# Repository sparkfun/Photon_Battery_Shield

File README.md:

SparkFun Photon Battery Shield
========================================

[*SparkFun Photon Battery Shield (DEV-13626)*](https://www.sparkfun.com/products/13626)

The [SparkFun Photon Battery Shield](https://www.sparkfun.com/products/13231) provides you with an easy way to power your Photon module with a Lithium polymer battery. Not only can the Battery Shield power you Photon but you will also be able to charge a LiPo bettery through it as well. The board comes with a JST connector for your single cell LiPo battery and utilizes the Photons on-board micro-USB connector for the charge input.

This battery shield uses a MCP73831 for LiPo charging and a MAX1704X for fuel gauging.

Repository Contents
-------------------

* **/Hardware** - Eagle design files (.brd, .sch)
* **/Production** - Production panel files (.brd)
* **/Libraries** - Firmware library and example code for the Particle Photon.

Documentation
--------------
* **[Hookup Guide](https://learn.sparkfun.com/tutorials/photon-battery-shield-hookup-guide)** - Hardware overview and example code.

Product Versions
----------------
* [DEV-13626](https://www.sparkfun.com/products/13626)- V1.0 release of the Photon Battery Shield.

License Information
-------------------
This product is _**open source**_! 

The **hardware** is released under [Creative Commons ShareAlike 4.0 International](https://creativecommons.org/licenses/by-sa/4.0/).

The **code**  license can be found in the source directory.

Please use, reuse, and modify these files as you see fit. Please maintain attribution to SparkFun Electronics and release anything derivative under the same license.

Distributed as-is; no warranty is given.

- Your friends at SparkFun.

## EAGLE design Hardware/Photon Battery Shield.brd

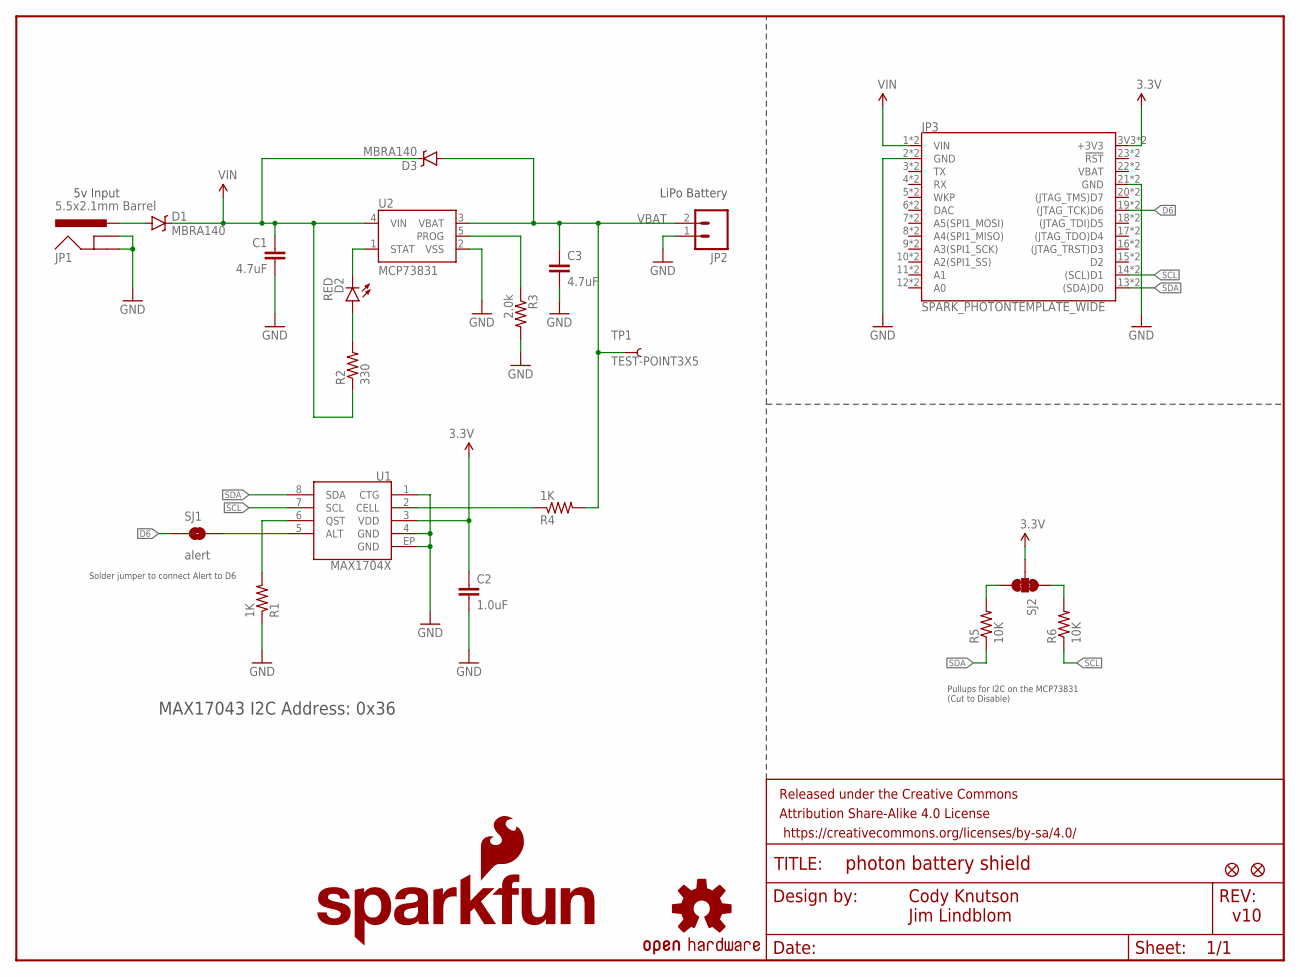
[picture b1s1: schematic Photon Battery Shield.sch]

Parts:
C1, C3: 4.7uF; 0603-CAP
C2: 1.0uF; 0603-CAP
D1, D3: MBRA140; SMA-DIODE
D2: RED; LED-0603
FID1, FID2: FIDUCIAL1X2; FIDUCIAL-1X2
FRAME1: FRAME-LETTER; CREATIVE_COMMONS
JP1: 5.5x2.1mm Barrel; POWER_JACK_SMD
JP2: M02-JST-2MM-SMT; JST-2-SMD
JP3: SPARK_PHOTONTEMPLATE_WIDE; SPARK_PHOTON_TEMPLATE_WIDE
LOGO2: OSHW-LOGOS; OSHW-LOGO-S
LOGO3: SFE_LOGO_NAME_FLAME.1_INCH; SFE_LOGO_NAME_FLAME_.1
R1, R4: 1K; 0603-RES
R2: 330; 0603-RES
R3: 2.0k; 0603-RES
R5, R6: 10K; 0603-RES
SJ1: alert; PAD-JUMPER-2-NO_YES_SILK
SJ2: JUMPER-PAD-3-NC_BY_TRACE; PAD-JUMPER-3-3OF3_NC_BY_TRACE_YES_SILK_FULL_BOX
TP1: TEST-POINT3X5; PAD.03X.05
U1: MAX1704X; TDFN-8
U2: MCP73831; SOT23-5

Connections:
3.3V: C2.1, JP3.3V3 (+3V3), JP3.24 (+3V3), SJ2.2, U1.3 (VDD)
D6: JP3.19 ((JTAG_TCK)D6), JP3.D6 ((JTAG_TCK)D6), SJ1.1
GND: C1.2, C2.2, C3.2, JP1.GND (GNDBREAK), JP1.P$4 (GND), JP2.1 (2), JP3.2 (GND), JP3.21 (GND), JP3.GND@0 (GND), JP3.GND@2 (GND), R1.1, R3.2, U1.1 (CTG), U1.4 (GND), U1.EP (GND), U2.2 (VSS)
unnamed: D2.A, R2.2
unnamed: D2.C, U2.1 (STAT)
unnamed: R3.1, U2.5 (PROG)
unnamed: SJ1.2, U1.5 (ALT)
unnamed: R4.1, U1.2 (CELL)
unnamed: R1.2, U1.6 (QST)
unnamed: R5.2, SJ2.3
unnamed: D1.A, JP1.VIN0 (PWR)
unnamed: R6.2, SJ2.1
SCL: JP3.14 ((SCL)D1), JP3.D1 ((SCL)D1), R6.1, U1.7 (SCL)
SDA: JP3.13 ((SDA)D0), JP3.D0 ((SDA)D0), R5.1, U1.8 (SDA)
VBAT: C3.1, D3.A, JP2.2 (1), R4.2, TP1.P$1, U2.3 (VBAT)
VIN: C1.1, D1.C, D3.C, JP3.1 (VIN), JP3.VIN, R2.1, U2.4 (VIN)

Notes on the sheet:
LiPo Battery
Cody Knutson Jim Lindblom
v10
MAX17043 I2C Address: 0x36
5v Input
Solder jumper to connect Alert to D6
Pullups for I2C on the MCP73831 (Cut to Disable)

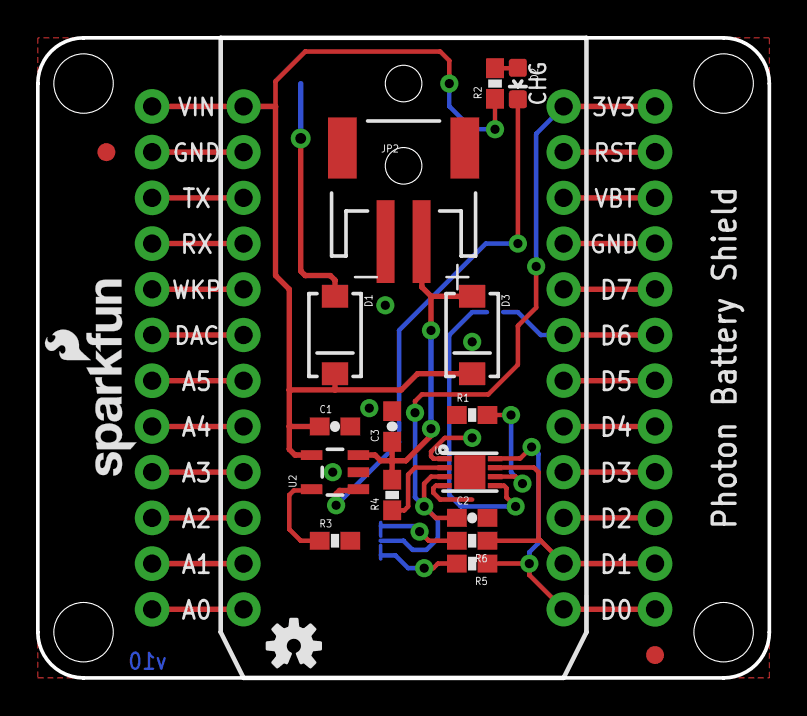
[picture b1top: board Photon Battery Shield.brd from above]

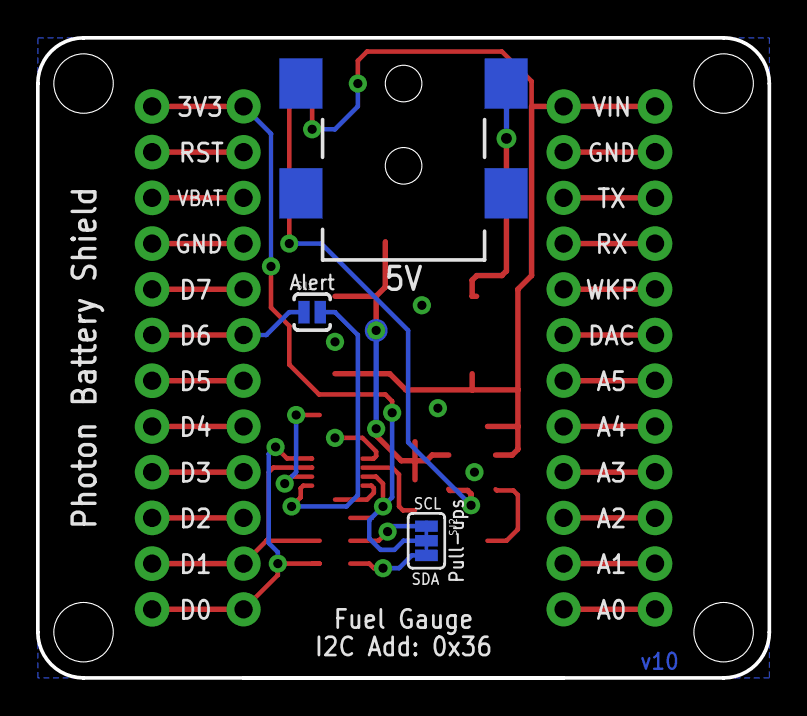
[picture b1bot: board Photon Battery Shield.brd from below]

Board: 2 copper layers, 40.6 x 35.6 mm, 25 parts (4 on the bottom side), 16 nets.

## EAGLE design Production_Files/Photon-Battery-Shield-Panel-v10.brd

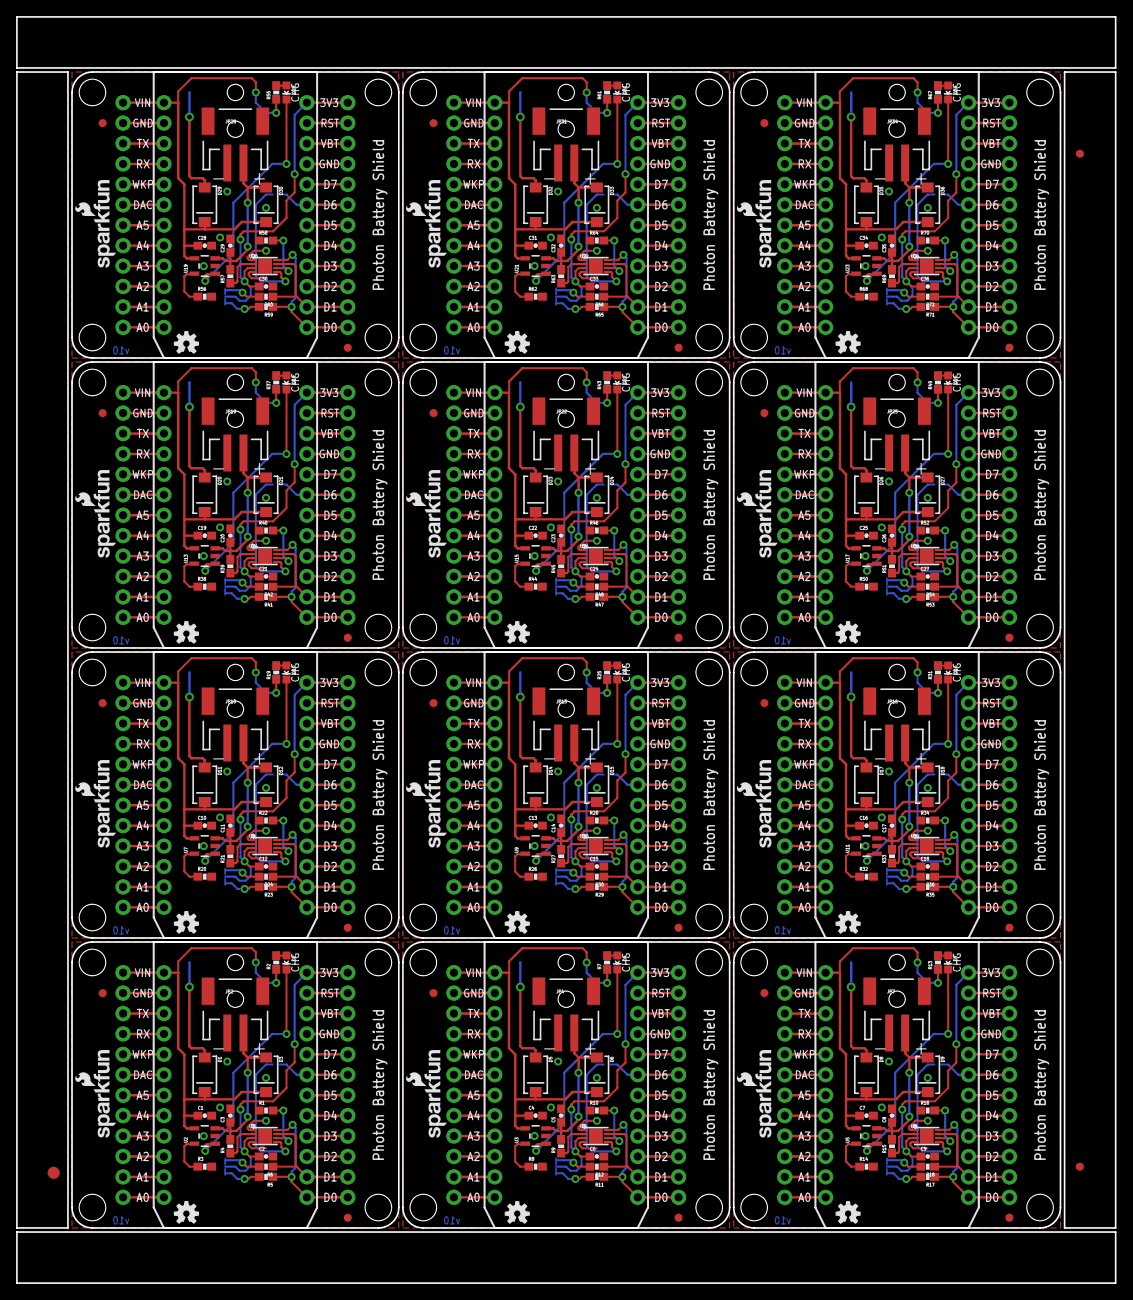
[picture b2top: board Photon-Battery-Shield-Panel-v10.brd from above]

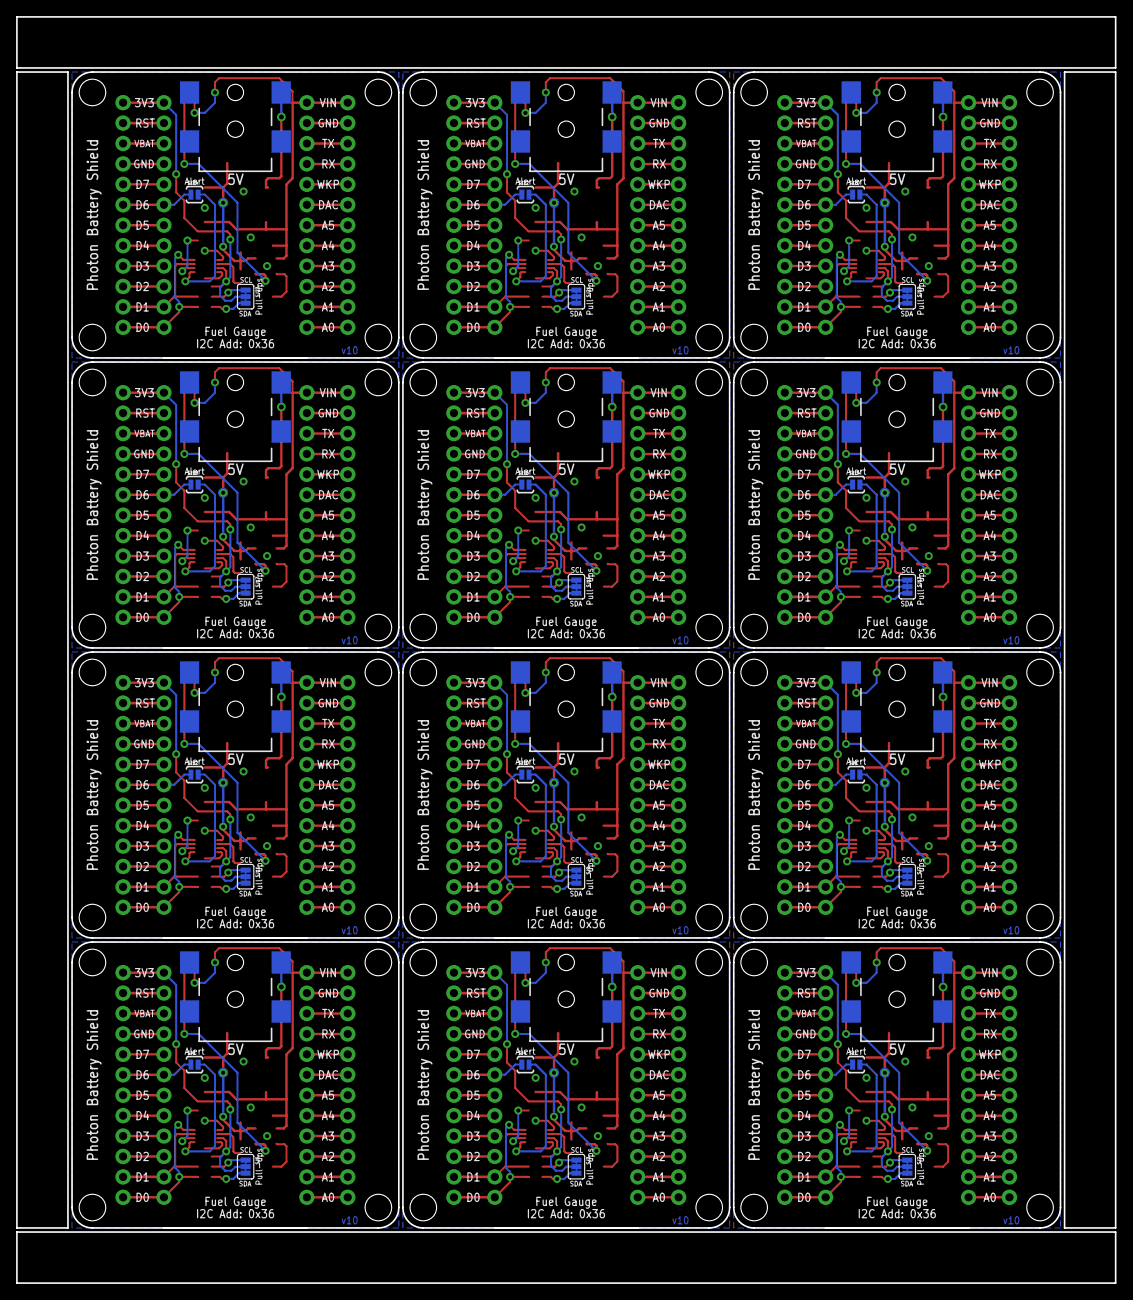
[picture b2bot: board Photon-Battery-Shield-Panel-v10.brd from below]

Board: 2 copper layers, 136.7 x 157.5 mm, 291 parts (48 on the bottom side), 192 nets.

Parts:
C1, C3, C4, C5, C7, C8, C10, C11, C13, C14, C16, C17, C19, C20, C22, C23, C25, C26, C28, C29, C31, C32, C34, C35: 4.7uF; 0603-CAP
C2, C6, C9, C12, C15, C18, C21, C24, C27, C30, C33, C36: 1.0uF; 0603-CAP
D1, D3, D5, D6, D8, D9, D11, D12, D14, D15, D17, D18, D20, D21, D23, D24, D26, D27, D29, D30, D32, D33, D35, D36: MBRA140; SMA-DIODE
D2, D4, D7, D10, D13, D16, D19, D22, D25, D28, D31, D34: RED; LED-0603
E$1: FIDUCIAL-1.5X3
E$4, E$5: FIDUCIAL-1X2
FID1, FID2, FID3, FID4, FID5, FID6, FID7, FID8, FID9, FID10, FID11, FID12, FID13, FID14, FID15, FID16, FID17, FID18, FID19, FID20, FID21, FID22, FID23, FID24: FIDUCIAL1X2; FIDUCIAL-1X2
JP1, JP6, JP9, JP12, JP15, JP18, JP21, JP24, JP27, JP30, JP33, JP36: 5.5x2.1mm Barrel; POWER_JACK_SMD
JP2, JP4, JP7, JP10, JP13, JP16, JP19, JP22, JP25, JP28, JP31, JP34: JST-2-SMD
JP3, JP5, JP8, JP11, JP14, JP17, JP20, JP23, JP26, JP29, JP32, JP35: SPARK_PHOTONTEMPLATE_WIDE; SPARK_PHOTON_TEMPLATE_WIDE
LOGO1, LOGO2, LOGO5, LOGO7, LOGO9, LOGO11, LOGO13, LOGO15, LOGO17, LOGO19, LOGO21, LOGO23: OSHW-LOGOS; OSHW-LOGO-S
LOGO3, LOGO4, LOGO6, LOGO8, LOGO10, LOGO12, LOGO14, LOGO16, LOGO18, LOGO20, LOGO22, LOGO24: SFE_LOGO_NAME_FLAME.1_INCH; SFE_LOGO_NAME_FLAME_.1
R1, R4, R9, R10, R15, R16, R21, R22, R27, R28, R33, R34, R39, R40, R45, R46, R51, R52, R57, R58, R63, R64, R69, R70: 1K; 0603-RES
R2, R7, R13, R19, R25, R31, R37, R43, R49, R55, R61, R67: 330; 0603-RES
R3, R8, R14, R20, R26, R32, R38, R44, R50, R56, R62, R68: 2.0k; 0603-RES
R5, R6, R11, R12, R17, R18, R23, R24, R29, R30, R35, R36, R41, R42, R47, R48, R53, R54, R59, R60, R65, R66, R71, R72: 10K; 0603-RES
SJ1, SJ4, SJ6, SJ8, SJ10, SJ12, SJ14, SJ16, SJ18, SJ20, SJ22, SJ24: alert; PAD-JUMPER-2-NO_YES_SILK
SJ2, SJ3, SJ5, SJ7, SJ9, SJ11, SJ13, SJ15, SJ17, SJ19, SJ21, SJ23: PAD-JUMPER-3-3OF3_NC_BY_TRACE_YES_SILK_FULL_BOX
TP1, TP2, TP3, TP4, TP5, TP6, TP7, TP8, TP9, TP10, TP11, TP12: TEST-POINT3X5; PAD.03X.05
U1, U4, U6, U8, U10, U12, U14, U16, U18, U20, U22, U24: MAX1704X; TDFN-8
U2, U3, U5, U7, U9, U11, U13, U15, U17, U19, U21, U23: MCP73831; SOT23-5

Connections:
3.3V: C2.1, JP3.3V3, JP3.24, SJ2.2, U1.3
3.3V1: C6.1, JP5.3V3, JP5.24, SJ3.2, U4.3
3.3V2: C9.1, JP8.3V3, JP8.24, SJ5.2, U6.3
3.3V3: C12.1, JP11.3V3, JP11.24, SJ7.2, U8.3
3.3V4: C15.1, JP14.3V3, JP14.24, SJ9.2, U10.3
3.3V5: C18.1, JP17.3V3, JP17.24, SJ11.2, U12.3
3.3V6: C21.1, JP20.3V3, JP20.24, SJ13.2, U14.3
3.3V7: C24.1, JP23.3V3, JP23.24, SJ15.2, U16.3
3.3V8: C27.1, JP26.3V3, JP26.24, SJ17.2, U18.3
3.3V9: C30.1, JP29.3V3, JP29.24, SJ19.2, U20.3
3.3V10: C33.1, JP32.3V3, JP32.24, SJ21.2, U22.3
3.3V11: C36.1, JP35.3V3, JP35.24, SJ23.2, U24.3
D1: JP5.19, JP5.D6, SJ4.1
D2: JP8.19, JP8.D6, SJ6.1
D3: JP11.19, JP11.D6, SJ8.1
D4: JP14.19, JP14.D6, SJ10.1
D5: JP17.19, JP17.D6, SJ12.1
D6: JP3.19, JP3.D6, SJ1.1
D7: JP20.19, JP20.D6, SJ14.1
D8: JP23.19, JP23.D6, SJ16.1
D9: JP26.19, JP26.D6, SJ18.1
D10: JP29.19, JP29.D6, SJ20.1
D11: JP32.19, JP32.D6, SJ22.1
D12: JP35.19, JP35.D6, SJ24.1
GND: C1.2, C2.2, C3.2, JP1.GND, JP1.P$4, JP2.1, JP3.2, JP3.21, JP3.GND@0, JP3.GND@2, R1.1, R3.2, U1.1, U1.4, U1.EP, U2.2
GND1: C4.2, C5.2, C6.2, JP4.1, JP5.2, JP5.21, JP5.GND@0, JP5.GND@2, JP6.GND, JP6.P$4, R8.2, R10.1, U3.2, U4.1, U4.4, U4.EP
GND2: C7.2, C8.2, C9.2, JP7.1, JP8.2, JP8.21, JP8.GND@0, JP8.GND@2, JP9.GND, JP9.P$4, R14.2, R16.1, U5.2, U6.1, U6.4, U6.EP
GND3: C10.2, C11.2, C12.2, JP10.1, JP11.2, JP11.21, JP11.GND@0, JP11.GND@2, JP12.GND, JP12.P$4, R20.2, R22.1, U7.2, U8.1, U8.4, U8.EP
GND4: C13.2, C14.2, C15.2, JP13.1, JP14.2, JP14.21, JP14.GND@0, JP14.GND@2, JP15.GND, JP15.P$4, R26.2, R28.1, U9.2, U10.1, U10.4, U10.EP
GND5: C16.2, C17.2, C18.2, JP16.1, JP17.2, JP17.21, JP17.GND@0, JP17.GND@2, JP18.GND, JP18.P$4, R32.2, R34.1, U11.2, U12.1, U12.4, U12.EP
GND6: C19.2, C20.2, C21.2, JP19.1, JP20.2, JP20.21, JP20.GND@0, JP20.GND@2, JP21.GND, JP21.P$4, R38.2, R40.1, U13.2, U14.1, U14.4, U14.EP
GND7: C22.2, C23.2, C24.2, JP22.1, JP23.2, JP23.21, JP23.GND@0, JP23.GND@2, JP24.GND, JP24.P$4, R44.2, R46.1, U15.2, U16.1, U16.4, U16.EP
GND8: C25.2, C26.2, C27.2, JP25.1, JP26.2, JP26.21, JP26.GND@0, JP26.GND@2, JP27.GND, JP27.P$4, R50.2, R52.1, U17.2, U18.1, U18.4, U18.EP
GND9: C28.2, C29.2, C30.2, JP28.1, JP29.2, JP29.21, JP29.GND@0, JP29.GND@2, JP30.GND, JP30.P$4, R56.2, R58.1, U19.2, U20.1, U20.4, U20.EP
GND10: C31.2, C32.2, C33.2, JP31.1, JP32.2, JP32.21, JP32.GND@0, JP32.GND@2, JP33.GND, JP33.P$4, R62.2, R64.1, U21.2, U22.1, U22.4, U22.EP
GND11: C34.2, C35.2, C36.2, JP34.1, JP35.2, JP35.21, JP35.GND@0, JP35.GND@2, JP36.GND, JP36.P$4, R68.2, R70.1, U23.2, U24.1, U24.4, U24.EP
unnamed: D2.A, R2.2
unnamed: D2.C, U2.1
unnamed: R3.1, U2.5
unnamed: SJ1.2, U1.5
unnamed: R4.1, U1.2
unnamed: R1.2, U1.6
unnamed: R5.2, SJ2.3
unnamed: D1.A, JP1.VIN0
unnamed: R6.2, SJ2.1
unnamed: D4.A, R7.2
unnamed: D4.C, U3.1
unnamed: R8.1, U3.5
unnamed: R9.1, U4.2
unnamed: R10.2, U4.6
unnamed: SJ4.2, U4.5
unnamed: D5.A, JP6.VIN0
unnamed: R11.2, SJ3.3
unnamed: R12.2, SJ3.1
unnamed: D7.A, R13.2
unnamed: D7.C, U5.1
unnamed: R14.1, U5.5
unnamed: R15.1, U6.2
unnamed: R16.2, U6.6
unnamed: SJ6.2, U6.5
unnamed: D8.A, JP9.VIN0
unnamed: R17.2, SJ5.3
unnamed: R18.2, SJ5.1
unnamed: D10.A, R19.2
unnamed: D10.C, U7.1
unnamed: R20.1, U7.5
unnamed: R21.1, U8.2
unnamed: R22.2, U8.6
unnamed: SJ8.2, U8.5
unnamed: D11.A, JP12.VIN0
unnamed: R23.2, SJ7.3
unnamed: R24.2, SJ7.1
unnamed: D13.A, R25.2
unnamed: D13.C, U9.1
unnamed: R26.1, U9.5
unnamed: R27.1, U10.2
unnamed: R28.2, U10.6
unnamed: SJ10.2, U10.5
unnamed: D14.A, JP15.VIN0
unnamed: R29.2, SJ9.3
unnamed: R30.2, SJ9.1
unnamed: D16.A, R31.2
unnamed: D16.C, U11.1
unnamed: R32.1, U11.5
unnamed: R33.1, U12.2
unnamed: R34.2, U12.6
unnamed: SJ12.2, U12.5
unnamed: D17.A, JP18.VIN0
unnamed: R35.2, SJ11.3
unnamed: R36.2, SJ11.1
unnamed: D19.A, R37.2
unnamed: D19.C, U13.1
unnamed: R38.1, U13.5
unnamed: R39.1, U14.2
unnamed: R40.2, U14.6
unnamed: SJ14.2, U14.5
unnamed: D20.A, JP21.VIN0
unnamed: R41.2, SJ13.3
unnamed: R42.2, SJ13.1
unnamed: D22.A, R43.2
unnamed: D22.C, U15.1
unnamed: R44.1, U15.5
unnamed: R45.1, U16.2
unnamed: R46.2, U16.6
unnamed: SJ16.2, U16.5
unnamed: D23.A, JP24.VIN0
unnamed: R47.2, SJ15.3
unnamed: R48.2, SJ15.1
unnamed: D25.A, R49.2
unnamed: D25.C, U17.1
unnamed: R50.1, U17.5
unnamed: R51.1, U18.2
unnamed: R52.2, U18.6
unnamed: SJ18.2, U18.5
unnamed: D26.A, JP27.VIN0
unnamed: R53.2, SJ17.3
unnamed: R54.2, SJ17.1
unnamed: D28.A, R55.2
unnamed: D28.C, U19.1
unnamed: R56.1, U19.5
unnamed: R57.1, U20.2
unnamed: R58.2, U20.6
unnamed: SJ20.2, U20.5
unnamed: D29.A, JP30.VIN0
unnamed: R59.2, SJ19.3
unnamed: R60.2, SJ19.1
unnamed: D31.A, R61.2
unnamed: D31.C, U21.1
unnamed: R62.1, U21.5
unnamed: R63.1, U22.2
unnamed: R64.2, U22.6
unnamed: SJ22.2, U22.5
unnamed: D32.A, JP33.VIN0
unnamed: R65.2, SJ21.3
unnamed: R66.2, SJ21.1
unnamed: D34.A, R67.2
unnamed: D34.C, U23.1
unnamed: R68.1, U23.5
unnamed: R69.1, U24.2
unnamed: R70.2, U24.6
unnamed: SJ24.2, U24.5
unnamed: D35.A, JP36.VIN0
unnamed: R71.2, SJ23.3
unnamed: R72.2, SJ23.1
SCL: JP3.14, JP3.D1, R6.1, U1.7
SCL1: JP5.14, JP5.D1, R12.1, U4.7
SCL2: JP8.14, JP8.D1, R18.1, U6.7
SCL3: JP11.14, JP11.D1, R24.1, U8.7
SCL4: JP14.14, JP14.D1, R30.1, U10.7
SCL5: JP17.14, JP17.D1, R36.1, U12.7
SCL6: JP20.14, JP20.D1, R42.1, U14.7
SCL7: JP23.14, JP23.D1, R48.1, U16.7
SCL8: JP26.14, JP26.D1, R54.1, U18.7
SCL9: JP29.14, JP29.D1, R60.1, U20.7
SCL10: JP32.14, JP32.D1, R66.1, U22.7
SCL11: JP35.14, JP35.D1, R72.1, U24.7
SDA: JP3.13, JP3.D0, R5.1, U1.8
SDA1: JP5.13, JP5.D0, R11.1, U4.8
SDA2: JP8.13, JP8.D0, R17.1, U6.8
SDA3: JP11.13, JP11.D0, R23.1, U8.8
SDA4: JP14.13, JP14.D0, R29.1, U10.8
SDA5: JP17.13, JP17.D0, R35.1, U12.8
SDA6: JP20.13, JP20.D0, R41.1, U14.8
SDA7: JP23.13, JP23.D0, R47.1, U16.8
SDA8: JP26.13, JP26.D0, R53.1, U18.8
SDA9: JP29.13, JP29.D0, R59.1, U20.8
SDA10: JP32.13, JP32.D0, R65.1, U22.8
SDA11: JP35.13, JP35.D0, R71.1, U24.8
VBAT: C3.1, D3.A, JP2.2, R4.2, TP1.P$1, U2.3
VBAT1: C5.1, D6.A, JP4.2, R9.2, TP2.P$1, U3.3
VBAT2: C8.1, D9.A, JP7.2, R15.2, TP3.P$1, U5.3
VBAT3: C11.1, D12.A, JP10.2, R21.2, TP4.P$1, U7.3
VBAT4: C14.1, D15.A, JP13.2, R27.2, TP5.P$1, U9.3
VBAT5: C17.1, D18.A, JP16.2, R33.2, TP6.P$1, U11.3
VBAT6: C20.1, D21.A, JP19.2, R39.2, TP7.P$1, U13.3
VBAT7: C23.1, D24.A, JP22.2, R45.2, TP8.P$1, U15.3
VBAT8: C26.1, D27.A, JP25.2, R51.2, TP9.P$1, U17.3
VBAT9: C29.1, D30.A, JP28.2, R57.2, TP10.P$1, U19.3
VBAT10: C32.1, D33.A, JP31.2, R63.2, TP11.P$1, U21.3
VBAT11: C35.1, D36.A, JP34.2, R69.2, TP12.P$1, U23.3
VIN: C1.1, D1.C, D3.C, JP3.1, JP3.VIN, R2.1, U2.4
VIN1: C4.1, D5.C, D6.C, JP5.1, JP5.VIN, R7.1, U3.4
VIN2: C7.1, D8.C, D9.C, JP8.1, JP8.VIN, R13.1, U5.4
VIN3: C10.1, D11.C, D12.C, JP11.1, JP11.VIN, R19.1, U7.4
VIN4: C13.1, D14.C, D15.C, JP14.1, JP14.VIN, R25.1, U9.4
VIN5: C16.1, D17.C, D18.C, JP17.1, JP17.VIN, R31.1, U11.4
VIN6: C19.1, D20.C, D21.C, JP20.1, JP20.VIN, R37.1, U13.4
VIN7: C22.1, D23.C, D24.C, JP23.1, JP23.VIN, R43.1, U15.4
VIN8: C25.1, D26.C, D27.C, JP26.1, JP26.VIN, R49.1, U17.4
VIN9: C28.1, D29.C, D30.C, JP29.1, JP29.VIN, R55.1, U19.4
VIN10: C31.1, D32.C, D33.C, JP32.1, JP32.VIN, R61.1, U21.4
VIN11: C34.1, D35.C, D36.C, JP35.1, JP35.VIN, R67.1, U23.4

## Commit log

2015-03-31 Added .BRD, and .SCH
2015-04-01 Re-layed out, needs traces done
2015-04-01 Completed
    Shield is done. Ready for review
2015-04-01 Completed and cleaned up directory
2015-04-02 Adjusting VIN route, GND vias. Checklist stuff.
    - Adding measures
    - Adding PROD_ID to some parts
    - Re-routed ALERT pin to D6
    - Added MAx17043 i2c address to schematic
    - Labeled jumpers ("Pullups" and "Alert")
    - Routed traces from fuel gauge directly out of pads. (Added tRestrict to
2015-04-02 Adding .gitignore to ignore Eagle backup files.
2015-04-08 Checklist Fixes
    (1) Added input voltage label on SCH
    (2) Added description for SJ1 in SCH
    (3) Added description for SJ2 in SCH
    (4) Fixed traces on R2, D1, and STAT pad on MCP
    (5) 3-way pull up now has SDA and SCL BPlace objects added next to the
    jumper
2015-05-05 Connecting GND - Photon pin 21 - to the GND plane.
2015-05-08 Updating Photon package to WIDE footprint. Defaulting SJ1 to open.
2015-05-22 Fixing board name silk.
2015-05-22 Small silkscreen changes.
2015-05-27 Adding test point to VBAT. Reducing bSilk on barrel jack to avoid going over board.
2015-05-28 created panel v10
2015-07-02 Standardizing README
2015-07-02 Squashed 'Libraries/Particle/' content from commit 7f8658a
    git-subtree-dir: Libraries/Particle
    git-subtree-split: 7f8658ace723ec92fe7f22ce0a70abb6c396f5a2
2015-07-02 Adding MAX17043 library.

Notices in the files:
parts and their libraries:
SparkFun-Passives: Licensing: CC v3.0 Share-Alike You are welcome to use this library for commercial purposes.
SparkFun-DiscreteSemi: Licensing: Creative Commons ShareAlike 4.0 International - https://creativecommons.org/licenses/by-sa/4.0
SparkFun-Aesthetics: Released under the Creative Commons
